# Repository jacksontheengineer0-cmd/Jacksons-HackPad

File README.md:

# Jacksons-HackPad
Hackpad for the Hack Club Project

CAD Model:

PCB & Schematic:

Everything should fit together using 4 M3 Bolts and heatset inserts.

BOM:
1x Seeed XIAO RP2040
10x Blank DSA keycaps (White)
2x SK6812 MINI-E LEDs

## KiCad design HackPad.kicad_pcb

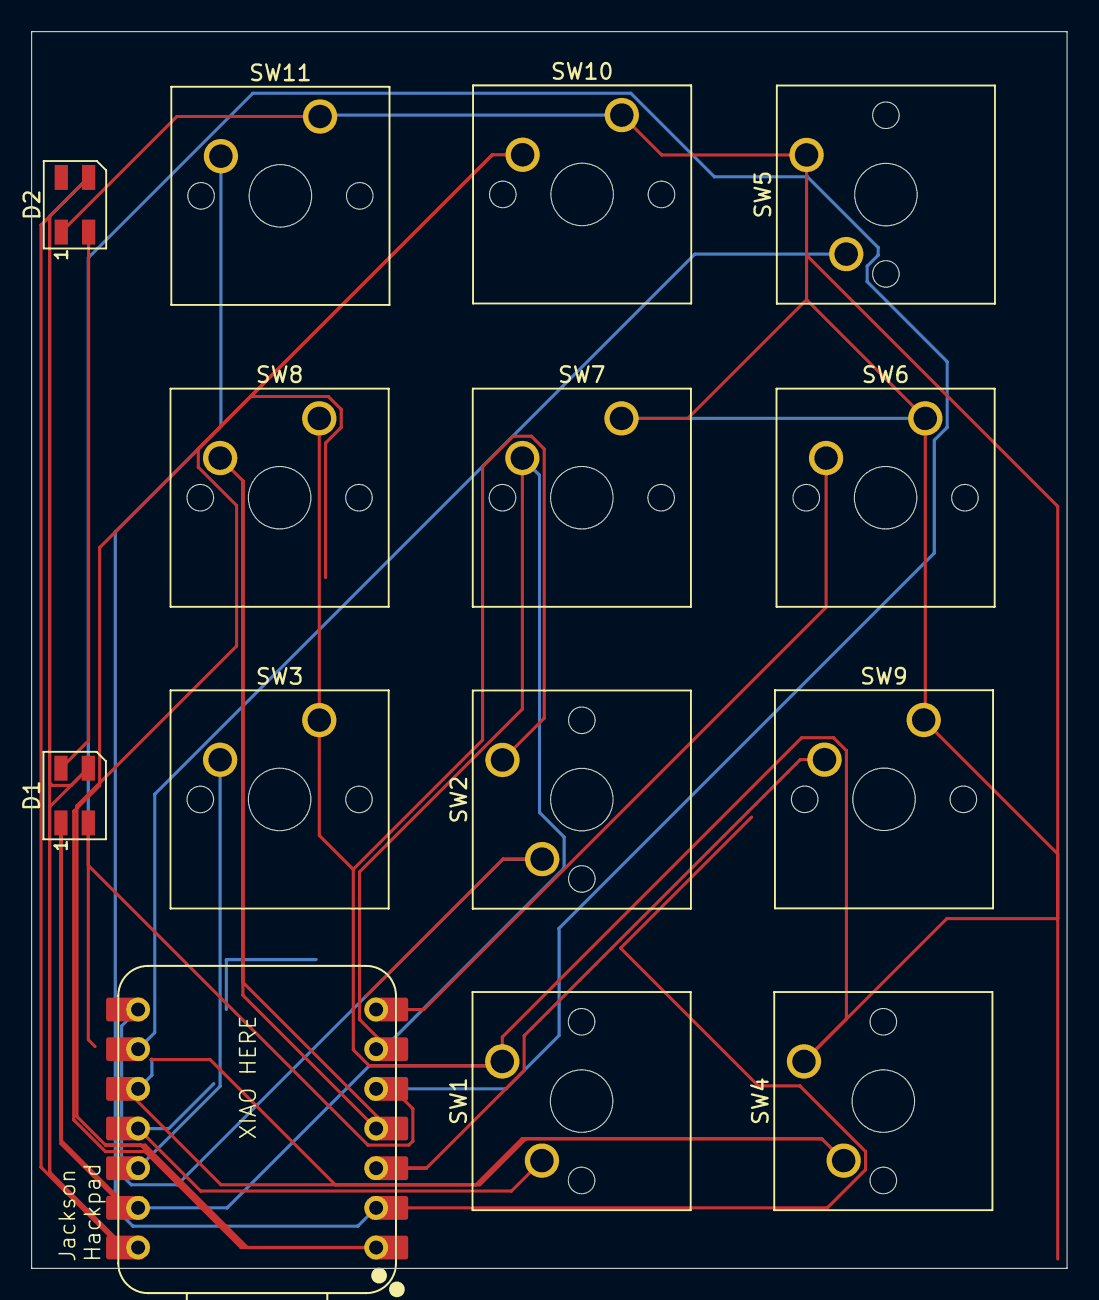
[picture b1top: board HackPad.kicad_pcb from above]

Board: 2 copper layers, 66.3 x 79.2 mm, 14 parts (0 on the bottom side), 15 nets.

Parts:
D1, D2: SK6812; LED_SK6812MINI_PLCC4_3.5x3.5mm_P1.75mm
SW1, SW2, SW3, SW4, SW5, SW6, SW7, SW8, SW9, SW10, SW11: SW_Push; SW_Cherry_MX_1.00u_PCB
U1: XIAO-RP2040-DIP

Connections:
+5V: D1.3 (VDD), D2.3 (VDD), U1.14 (VBUS)
GND: D1.1 (VSS), D2.1 (VSS), SW1.1, SW2.1, SW3.1, SW4.1, SW5.1, SW6.1, SW7.1, SW8.1, SW9.1, SW10.1, SW11.1, U1.13 (GND)
unnamed: D1.2 (DIN), U1.5 (GPIO6/SDA)
unnamed: D1.4 (DOUT), D2.2 (DIN)
unnamed: SW3.2, U1.12 (3V3)
unnamed: SW6.2, U1.7 (GPIO0/TX)
unnamed: SW2.2, U1.8 (GPIO1/RX)
unnamed: SW5.2, U1.9 (GPIO2/SCK)
unnamed: SW1.2, U1.11 (GPIO3/MOSI)
unnamed: SW4.2, U1.10 (GPIO4/MISO)
unnamed: SW7.2, U1.6 (GPIO7/SCL)
unnamed: SW10.2, U1.1 (GPIO26/ADC0/A0)
unnamed: SW11.2, U1.2 (GPIO27/ADC1/A1)
unnamed: SW9.2, U1.3 (GPIO28/ADC2/A2)
unnamed: SW8.2, U1.4 (GPIO29/ADC3/A3)

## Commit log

2026-01-20 Update README with CAD Model section
    Add CAD Model section to README
2026-01-20 Update reference to Orpheuspad in README
2026-01-20 Revise CAD model images and assembly notes
    Updated CAD model images and clarified assembly instructions.
2026-01-20 Replace CAD model image with a new screenshot
    Updated the CAD model image in the README.
2026-01-20 Initialize firmware for KMK keyboard setup
2026-01-20 Add BOM section to README
    Added Bill of Materials (BOM) section with components.
2026-01-20 Update firmware
2026-01-20 Create Hackpad Case
2026-01-21 Create Hackpad PCB & Schematic
2026-01-21 Update bolt count in assembly instructions
2026-01-21 Update Hackpad Case
2026-01-21 Remove Hackpad Case file
2026-01-21 Add Hackpad Bottom Final.step file
2026-01-21 Add Hackpad Top Final.step file
2026-01-21 Rename HackPad.kicad_pcb to Hackpad PCB/Kicad_PCB
2026-01-21 Rename HackPad.kicad_pro to Hackpad PCB/Kicad_pro
2026-01-21 Rename HackPad.kicad_sch to Hackpad PCB/Kicad_sch
2026-01-21 Add additional pins to the PINS list
2026-01-21 Rename Kicad_PCB to Hackpad.kcad_PCB
2026-01-21 Rename Kicad_pro to Hackpad.kicad_pro
2026-01-21 Rename Kicad_sch to Hackpad.kicad_sch
2026-01-21 Rename Hackpad.kcad_PCB to Hackpad.kicad_PCB
2026-01-21 Add Bottom Final.step to Hackpad Case Parts
2026-01-21 Add Top Final.step to Hackpad Case Parts
2026-01-21 Update BOM to correct the number of keycaps
2026-01-21 Rename Hackpad Bottom Case.step to Hackpad CAD/Hackpad Bottom Case.step
2026-01-22 Rename Hackpad Top Case.step to Hackpad CAD/Hackpad Top Case.step
2026-01-22 Rename Hackpad.kicad_PCB to Hackpad.kicad_pcb
2026-01-22 Fix pin list formatting in main.py
